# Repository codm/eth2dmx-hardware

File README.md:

# Ethernet DMX Bridge

The Ethernet DMX Bridge is an open-source hardware solution to generate DMX signals mainly for lightning applications.

It is based on the work from the [LoxForum](https://www.loxforum.com/forum/faqs-tutorials-howto-s/34948-g%C3%BCnstige-und-bessere-alternative-zur-dmx-extension), a german Loxone community. The Software ist mainly developed by Robert Lechner: https://sourceforge.net/p/udptodmx/code/HEAD/tree/trunk/ with extensions from us (cod.m GmbH).
The development of this software has moved to github: https://github.com/LechnerRobert/UDPtoDMX/

The hardware was developed to be a finished product (including CE and RoHS) which can be mounted in a DIN-Rail enclosure - an electric cabinet - so that electricians and alike have not to build their own using some dodgy hardware and perfboards.

To buy one, visit https://shop.codm.de/module/8/ethernet-dmx-bridge-v0.4

## Hardware

We've built it with a wide input voltage range (7-36V), protection for the RS485/DMX-Bus and an easy to use DHCP option with an unique EUID48. Also we've added a short circuit protection.

The second big thing was power consumption. We are currently using not more tha 0.34W for the complete unit. Achieved is this by using WizNets W5500 instead of the (older) W5100 and by using the original MAX485 from Maxim.

You can read about the built in Patrik Mayer's blog: https://allgeek.de/2018/07/22/professionelle-ethernet-dmx-bridge-udp/ (german)

## Software

We've used mainly the original software from Robert but extended it for the EUDI48 use and maintaining the DHCP IP address. 

For the network part we rely on Paull Stoffregens marvelous ethernet library, which is meanwhile the one shipped with the arduino IDE by default.
As this library currently does not have a way to set the ethernet hostname, we've [forked](https://github.com/codm/Ethernet) the library and added it. 

Please follow Robert's instructions on compiling and use our version of the libraries when enabling certain features.

## Legal

We do __not__ allow reproduction of the hardware without our consent. If you wan't to use the schematics and/or board in your own private project, feel free. But don't use __any__ of this in a commercial manner without contacting us!

(c) cod.m GmbH, 2018, Germany - CC-BY-SA

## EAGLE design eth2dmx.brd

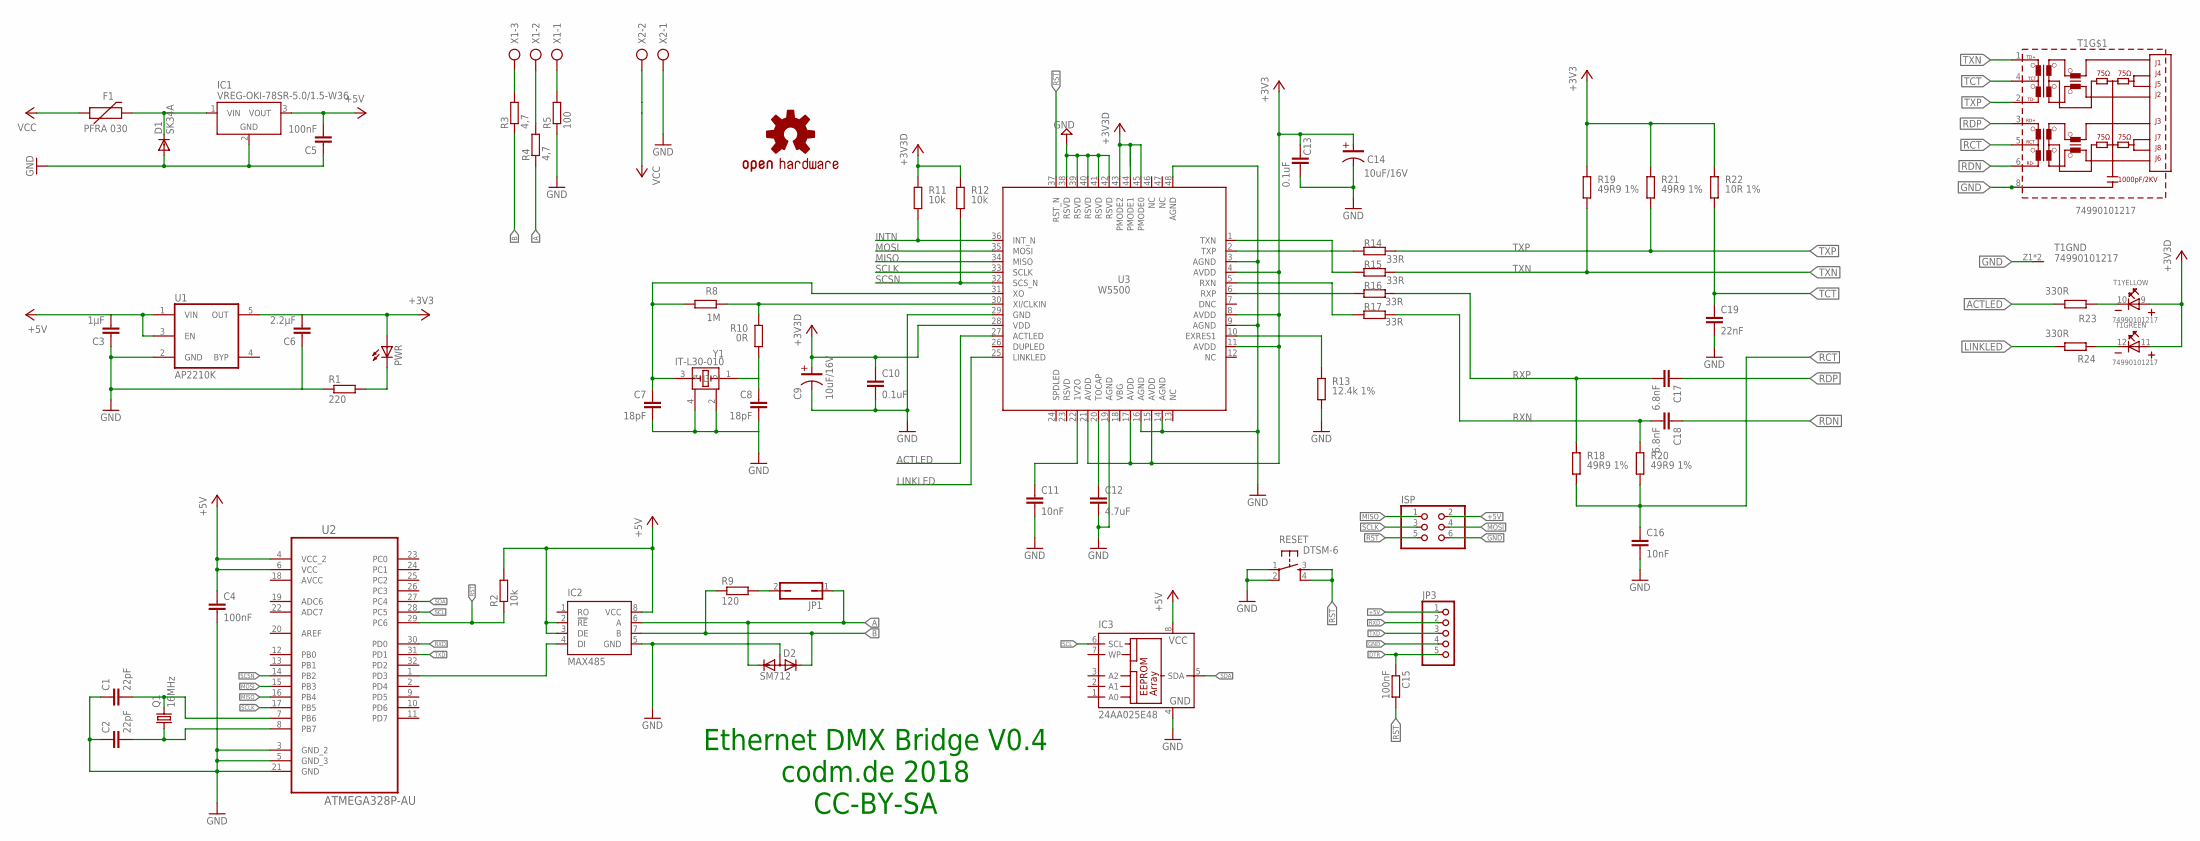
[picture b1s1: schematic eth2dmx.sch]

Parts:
C1, C2: 22pF; C0805
C3: 1µF; C0805
C4, C5: 100nF; C0805
C6: 2.2µF; C0805
C7, C8: 18pF; C0805
C9, C14: 10uF/16V; C-3216(TANTAL)
C10, C13: 0.1uF; C0805
C11, C16: 10nF; C0805
C12: 4.7uF; C0805
C15: 100nF; R0805
C17, C18: 6.8nF; C0805
C19: 22nF; C0805
D1: SK34A; DO214AC
D2: SM712; SOT23
F1: PFRA 030; PTH
IC1: VREG-OKI-78SR-5.0/1.5-W36; OKI-78SR
IC2: MAX485; SOIC8
IC3: 24AA025E48; SO-08
ISP: PINHD-2X3; 2X03
JP1: JP1Q; JP1
JP3: PINHD-1X5; 1X05
LOGO1: OSHW-LOGOM; OSHW-LOGO-M
PWR: LEDCHIP-LED0805; CHIP-LED0805
Q1: 16MHz; HC49U70
R1: 220; R0805
R2, R11, R12: 10k; R0805
R3, R4: 4,7; R0805
R5: 100; R0805
R8: 1M; R0805
R9: 120; R0805
R10: 0R; R0805
R13: 12.4k 1%; R0805
R14, R15, R16, R17: 33R; R0805
R18, R19, R20, R21: 49R9 1%; R0805
R22: 10R 1%; R0805
R23, R24: 330R; R0805
RESET: DTSM-6
T1: 74990101217; 74990111217
U1: AP2210K; SOT23-5
U2: ATMEGA328P-AU; QFP80P900X900X120-32N
U3: W5500
X1: AK500/3
X2: AK500/2
Y1: IT-L30-010

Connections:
+3V3: C6.2, C9.1, C10.1, C13.1, C14.1, PWR.A, R11.2, R12.2, R19.2, R21.2, R22.2, T1.9 (A), T1.11 (A), U1.5 (OUT), U3.4 (AVDD), U3.8 (AVDD), U3.11 (AVDD), U3.15 (AVDD), U3.17 (AVDD), U3.21 (AVDD), U3.28 (VDD), U3.43 (PMODE2), U3.44 (PMODE1), U3.45 (PMODE0)
+5V: C3.2, C4.1, C5.2, IC1.3 (VOUT), IC2.2 (!RE), IC2.3 (DE), IC2.8 (VCC), IC3.8 (VCC), ISP.2, JP3.1, R2.2, U1.1 (VIN), U1.3 (EN), U2.4 (VCC_2), U2.6 (VCC)
A: D2.1 (K1), IC2.6 (A), JP1.1, R4.1
ACTLED: R23.1, U3.27 (ACTLED)
AVCC: U2.18 (AVCC)
B: D2.2 (K2), IC2.7 (B), R3.1, R9.1
DOUT: IC2.4 (DI), U2.1 (PD3)
DTR: C15.1, JP3.5
GND: C1.1, C2.1, C3.1, C4.2, C5.1, C6.1, C7.2, C8.2, C9.2, C10.2, C11.2, C12.2, C13.2, C14.2, C16.2, C19.2, D1.A, D2.3 (A), IC1.2 (GND), IC2.5 (GND), IC3.4 (GND), ISP.6, JP3.4, R1.1, R5.1, R13.1, RESET.1, RESET.2, T1.8, T1.Z1 (GND), T1.Z2 (GND), U1.2 (GND), U2.3 (GND_2), U2.5 (GND_3), U2.21 (GND), U3.3 (AGND), U3.9 (AGND), U3.14 (AGND), U3.16 (AGND), U3.19 (AGND), U3.29 (GND), U3.38 (RSVD), U3.39 (RSVD), U3.40 (RSVD), U3.41 (RSVD), U3.42 (RSVD), U3.48 (AGND), X2.1, Y1.2, Y1.4
INTN: R11.1, U3.36 (INT_N)
LINKLED: R24.1, U3.25 (LINKLED)
MISO: ISP.1, U2.16 (PB4), U3.34 (MISO)
MOSI: ISP.4, U2.15 (PB3), U3.35 (MOSI)
unnamed: C12.1, U3.20 (TOCAP)
unnamed: C2.2, Q1.1, U2.8 (PB7)
unnamed: C1.2, Q1.2, U2.7 (PB6)
unnamed: R5.2, X1.1
unnamed: R3.2, X1.3
unnamed: R4.2, X1.2
unnamed: PWR.C, R1.2
unnamed: D1.C, F1.P$2 (2), IC1.1 (VIN)
unnamed: R8.2, R10.2, U3.30 (XI/CLKIN)
unnamed: JP1.2, R9.2
unnamed: C11.1, U3.22 (1V2O)
unnamed: R13.2, U3.10 (EXRES1)
unnamed: R16.2, U3.6 (RXP)
unnamed: C7.1, R8.1, U3.31 (XO), Y1.3
unnamed: R17.2, U3.5 (RXN)
unnamed: R14.2, U3.2 (TXP)
unnamed: R15.2, U3.1 (TXN)
unnamed: C8.1, R10.1, Y1.1
unnamed: R23.2, T1.10 (K)
unnamed: R24.2, T1.12 (K)
RCT: C16.1, R18.1, R20.1, T1.5 (RCT)
RDN: C18.1, T1.6 (RD-)
RDP: C17.1, T1.3 (RD+)
RST: C15.2, ISP.5, R2.1, RESET.3, RESET.4, U2.29 (PC6), U3.37 (RST_N)
RXD: JP3.2, U2.30 (PD0)
RXN: C18.2, R17.1, R20.2
RXP: C17.2, R16.1, R18.2
SCL: IC3.6 (SCL), U2.28 (PC5)
SCLK: ISP.3, U2.17 (PB5), U3.33 (SCLK)
SCSN: R12.1, U2.14 (PB2), U3.32 (SCS_N)
SDA: IC3.5 (SDA), U2.27 (PC4)
TCT: C19.1, R22.1, T1.4 (TCT)
TXD: JP3.3, U2.31 (PD1)
TXN: R15.1, R19.1, T1.1 (TD+)
TXP: R14.1, R21.1, T1.2 (TD-)
VCC: F1.P$1 (1), X2.2

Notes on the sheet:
Ethernet DMX Bridge V0.4 codm.de 2018 CC-BY-SA

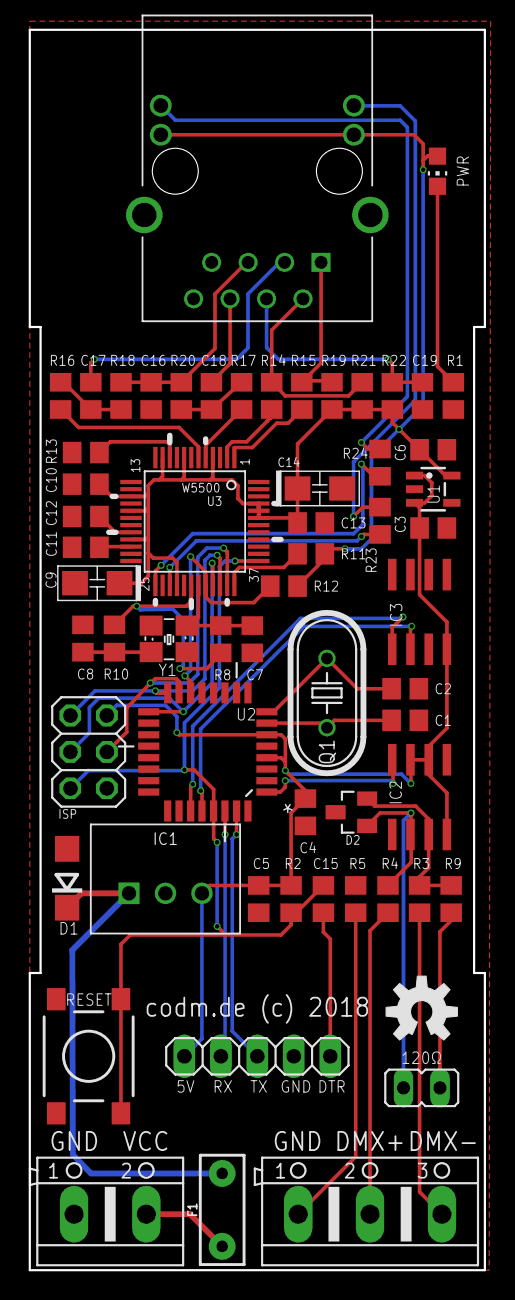
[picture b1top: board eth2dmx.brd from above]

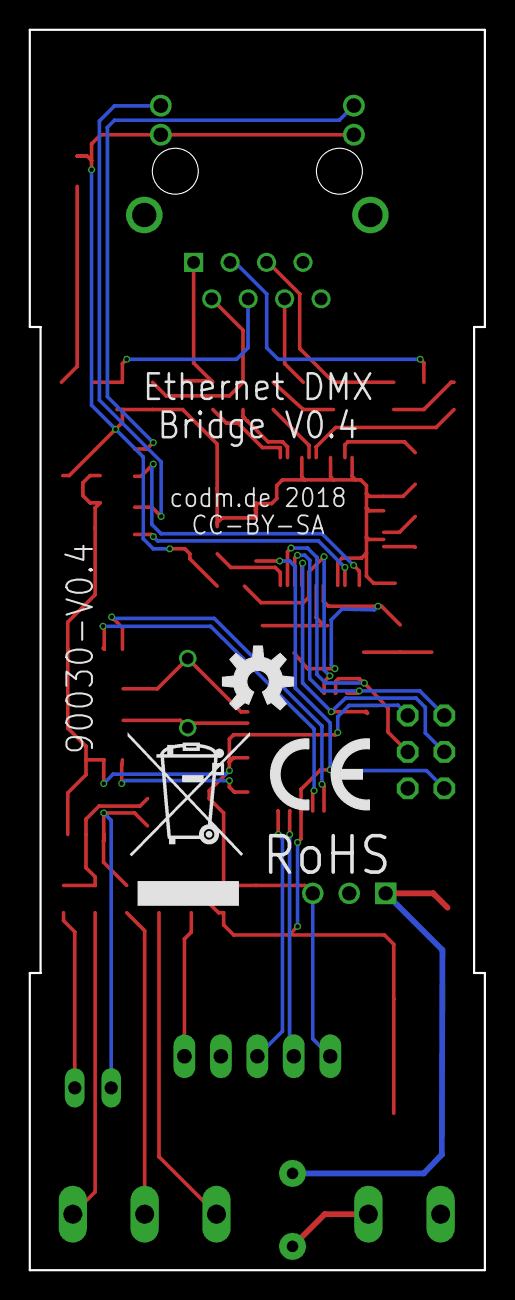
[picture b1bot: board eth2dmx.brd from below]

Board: 2 copper layers, 31.7 x 86.4 mm, 64 parts (3 on the bottom side), 48 nets.

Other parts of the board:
LOGO2: OSHW-LOGOM; OSHW-LOGO-M
U$1: CE_5MM
U$3: WEEE-LOGO-8MM

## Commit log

2019-08-12 cleanup for github
2019-08-12 typos
2019-08-12 clarify legal part
2019-08-12 typo

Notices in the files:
eth2dmx.brd:
codm.de (c) 2018
parts and their libraries:
SignalCommunications: Copyright: Würth Elektronik
SparkFun-Aesthetics: Licensing: Creative Commons ShareAlike 4.0 International - https://creativecommons.org/licenses/by-sa/4.0
